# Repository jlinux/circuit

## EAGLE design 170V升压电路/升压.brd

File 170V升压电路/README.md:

这个电路是12V到170V的升压电路，这个是参考[辉光钟之家](http://www.nixieclock.org/)驱动辉光管的升压电路。

我自己买了辉光管，所以准备学习一下。

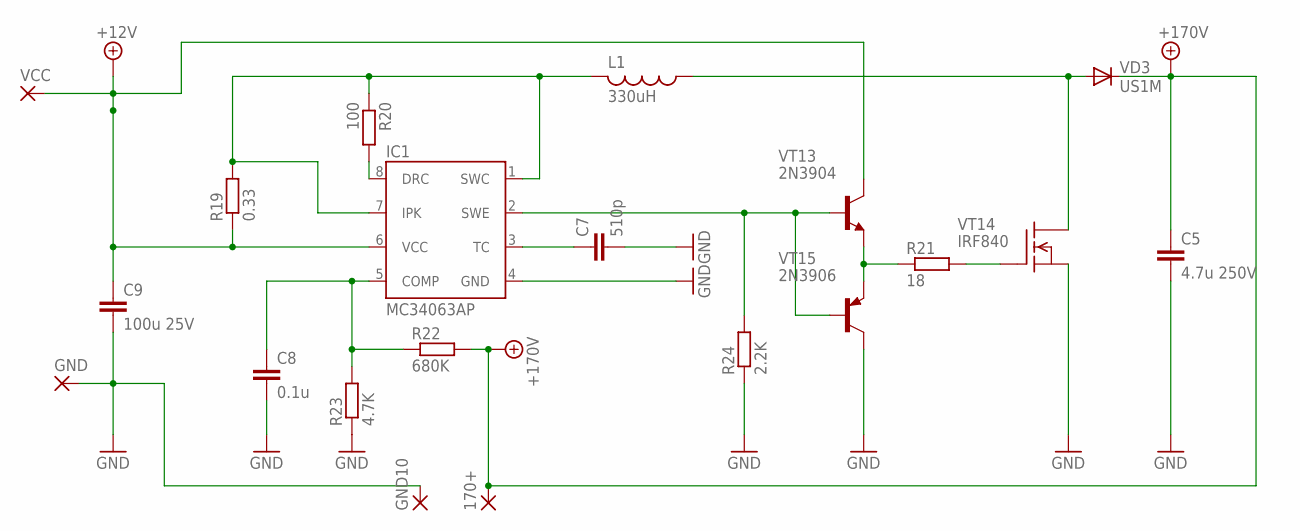
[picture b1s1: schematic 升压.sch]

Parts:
170+: 2,54/0,8
C5: 4.7u 250V; C050-025X075
C7: 510p; C050-025X075
C8: 0.1u; C050-025X075
C9: 100u 25V; C050-025X075
GND, GND10: 2,54/0,8
IC1: MC34063AP; DIL-08
L1: 330uH; 0207/10
R19: 0.33; 0204/5
R20: 100; 0204/5
R21: 18; 0204/5
R22: 680K; 0204/5
R23: 4.7K; 0204/5
R24: 2.2K; 0204/5
VCC: 2,54/0,8
VD3: US1M; DO41-10
VT13: 2N3904; TO92
VT14: IRF840; TO220
VT15: 2N3906; TO92

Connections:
+12V: C9.1, IC1.6 (VCC), R19.1, VCC.1, VT13.1 (C)
+UB: 170+.1, C5.1, R22.2, VD3.C
GND: C5.2, C7.2, C8.2, C9.2, GND.1, GND10.1, IC1.4 (GND), R23.1, R24.1, VT14.3 (S), VT15.1 (C)
unnamed: IC1.8 (DRC), R20.2
unnamed: C7.1, IC1.3 (TC)
unnamed: C8.1, IC1.5 (COMP), R22.1, R23.2
unnamed: L1.1, VD3.A, VT14.2 (D)
unnamed: IC1.1 (SWC), IC1.7 (IPK), L1.2, R19.2, R20.1
unnamed: IC1.2 (SWE), R24.2, VT13.2 (B), VT15.2 (B)
unnamed: R21.1, VT13.3 (E), VT15.3 (E)
unnamed: R21.2, VT14.1 (G)

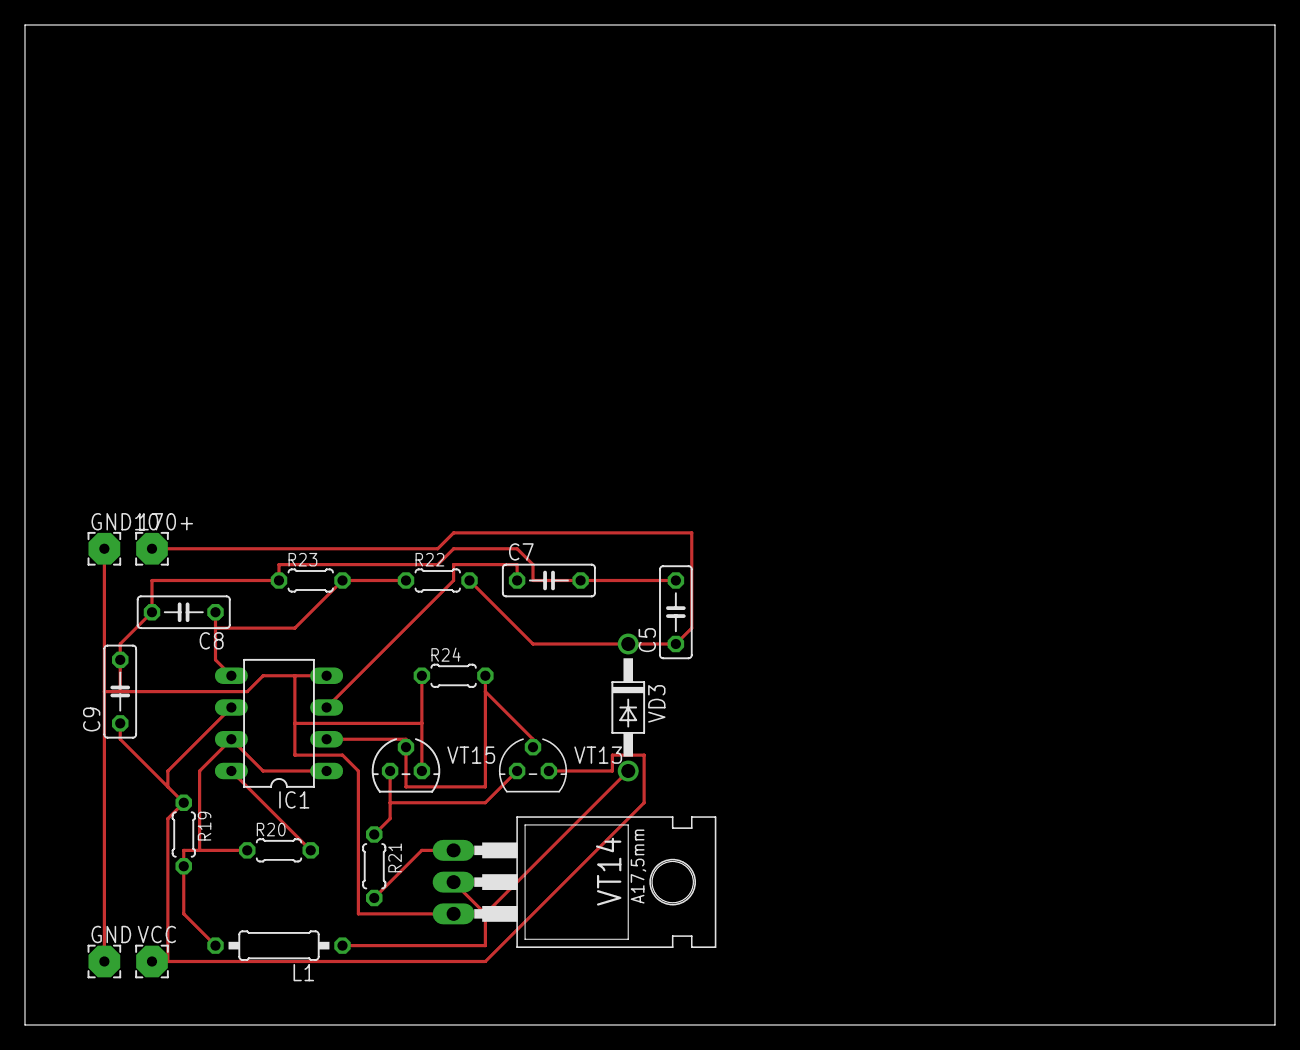
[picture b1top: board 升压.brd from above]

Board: 2 copper layers, 100.0 x 80.0 mm, 20 parts (0 on the bottom side), 11 nets.

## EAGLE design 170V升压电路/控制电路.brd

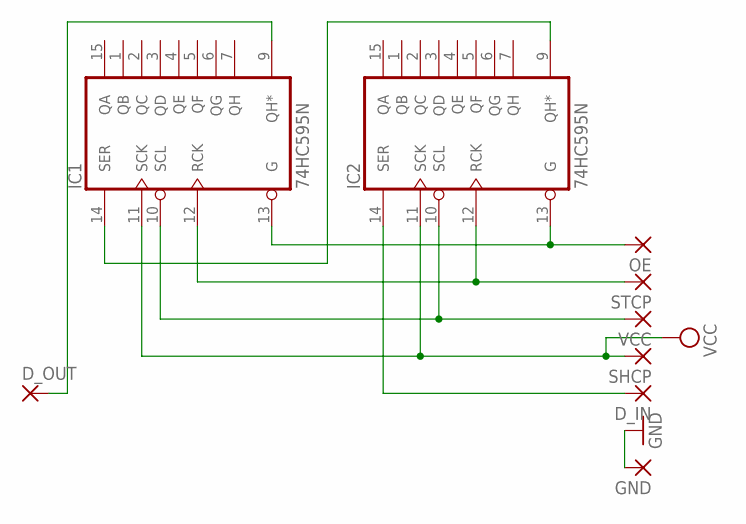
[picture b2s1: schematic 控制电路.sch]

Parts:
D_IN: 1,6/0,8
D_OUT: 1,6/0,8
GND: 1,6/0,8
IC1, IC2: 74HC595N; DIL16
OE: 1,6/0,8
SHCP: 1,6/0,8
STCP: 1,6/0,8
VCC: 1,6/0,8

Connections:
GND: GND.1, IC1.8 (GND), IC2.8 (GND)
unnamed: IC1.13 (G), IC2.13 (G), OE.1
unnamed: IC1.12 (RCK), IC2.12 (RCK), STCP.1
unnamed: IC1.10 (SCL), IC2.10 (SCL), VCC.1
unnamed: IC1.14 (SER), IC2.9 (QH*)
unnamed: D_IN.1, IC2.14 (SER)
unnamed: D_OUT.1, IC1.9 (QH*)
VCC: IC1.11 (SCK), IC1.16 (VCC), IC2.11 (SCK), IC2.16 (VCC), SHCP.1

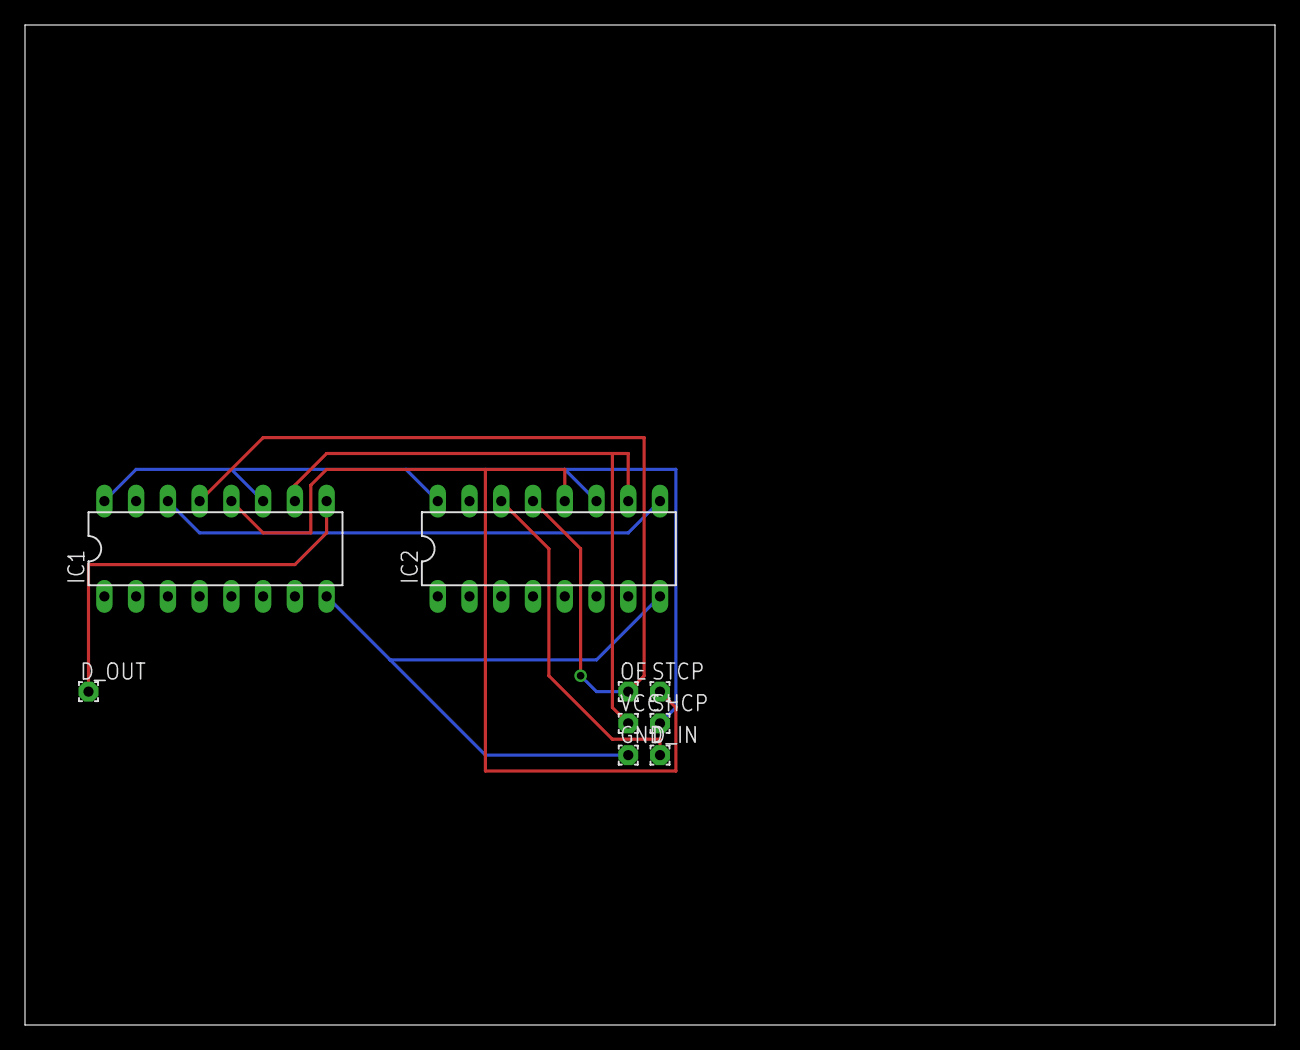
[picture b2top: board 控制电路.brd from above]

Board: 2 copper layers, 100.0 x 80.0 mm, 9 parts (0 on the bottom side), 8 nets.

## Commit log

2013-04-11 增加升压电路
2013-04-11 修改美化一下
2013-04-11 哈哈 有点好看了。
2013-04-11 持续优化
2013-04-11 添加了新的控制电路
2013-04-13 修改电容元器件的尺寸
